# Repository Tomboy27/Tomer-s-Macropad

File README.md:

# Tomer's Macropad

This is a custom, programmable macropad powered by a Seeed Studio XIAO RP2040, KMK firmware, a custom PCB, and a 3D-printed case. This is my first hardware project, completed to improve both my engineering skills and my day to day life with shortcuts and a rotary encoder.

## What It Does

- 6 mechanical keys with Cherry MX switches and DSA keycaps
- Rotary encoder (EC11) for volume up/down and mute
- Custom firmware using KMK (CircuitPython-based mechanical keyboard firmware)
- PC-side macros for application-specific shortcuts
- Custom PCB and 3D-printed case

## Bill of Materials

- 6× Cherry MX Switches
- 6× DSA keycaps
- 1× Seeed Studio XIAO RP2040
- 4× 1N4148 diodes (through-hole)
- 1× EC11 rotary encoder
- 4× M3×16mm screws
- 1× case (2 printed parts, STEP file in `CAD/`)

## Features

### Firmware

- One primary layer with 7 keys: A, B, C, D, E, F, and MUTE
- Rotary encoder:
  - Turn clockwise for volume up (`KC.VOLU`)
  - Turn counter-clockwise for volume down (`KC.VOLD`)

### PC Macros

- Custom macros configured on my PC for workflow shortcuts such as an auto clicker, opening certain apps, etc.

## Hardware

### Wiring

- See wiring diagrams below!
- The XIAO RP2040 is used as the main microcontroller.
- Keys are wired with diodes and directly to GPIO pins.
- Rotary encoder is wired to `GP0` (A) and `GP1` (B).

### PCB

- Custom PCB designed for the macropad.
- Screenshot of the PCB layout is shown below.

### Case

- 3D-printed case made of two parts.
- STEP file available in `CAD/`.
- Assembly uses 4× M3×16mm screws.

## Assembly / Build Steps

Coming Soon...

## Firmware

- Written in CircuitPython using the KMK library.
- Main file: `macropad.py` in the repo root.
- Keymap: 1 layer with 7 inputs (6 keys + encoder button).
- Encoder actions: volume up/down.

To flash:

1. Put the XIAO RP2040 in bootloader mode (double-press reset or connect BOOT0).
2. Copy `macropad.py` to the `CIRCUITPY` drive.
3. Ensure the `KMK` library is installed on the CIRCUITPY drive.

## Lessons Learned

- First hardware project: learned PCB layout, soldering, and embedded firmware for mechanical keyboards using KMK and CircuitPython.
- Discovered how rotary encoders work and how to integrate them into KMK firmware.
- Improved Github skills (first repo as well!)
- Overall increase in problem solving through the many issues that came with the building process.

## Future Improvements

- Add a second firmware layer for app-specific shortcuts.
- Add an OLED display.
- Improve the keymap with more complex macros in the firmware instead of PC-side macros.
- Document the build process with more photos and quantitative test results (e.g., debounce behavior, latency).

## Photos

Here is a picture of the final HackPad, schematic, PCB, and case model!

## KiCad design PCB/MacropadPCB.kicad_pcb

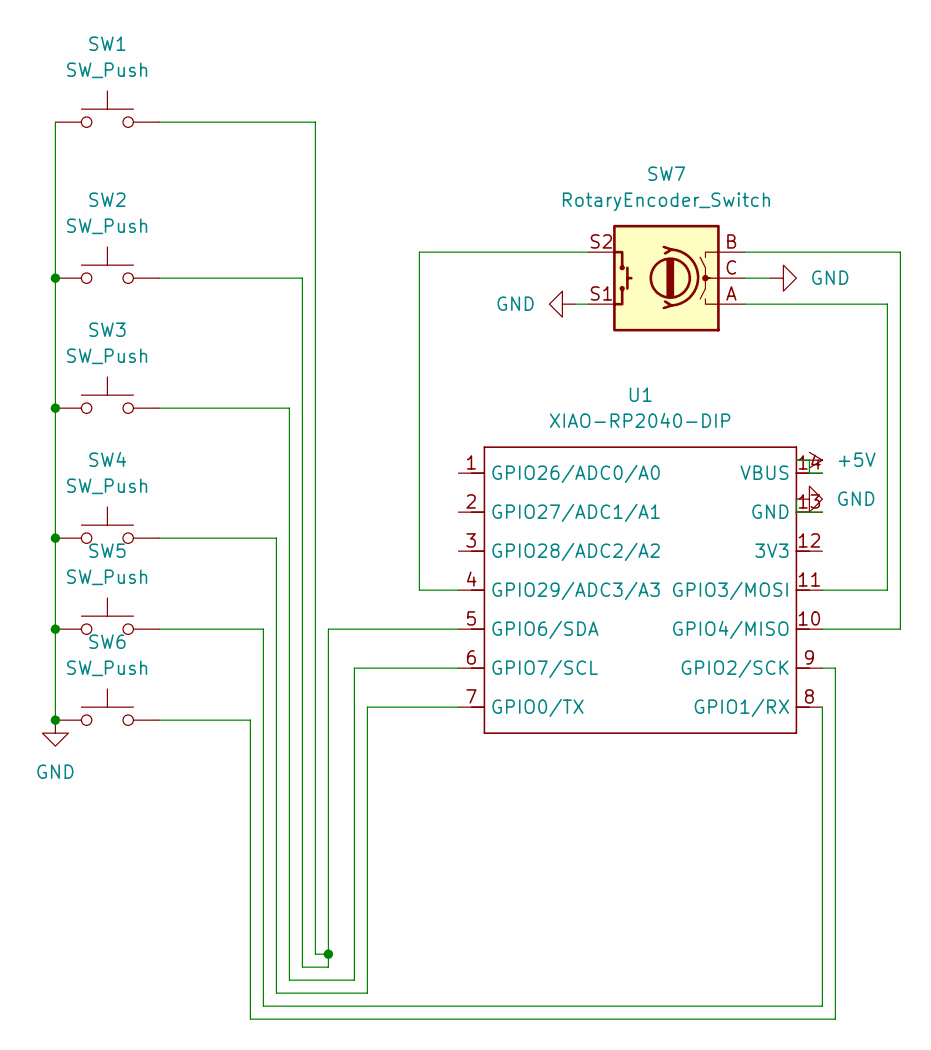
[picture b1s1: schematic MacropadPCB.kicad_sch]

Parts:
SW1, SW2, SW3, SW4, SW5, SW6: SW_Push; SW_Cherry_MX_1.00u_PCB
SW7: RotaryEncoder_Switch; RotaryEncoder_Alps_EC11E-Switch_Vertical_H20mm
U1: XIAO-RP2040-DIP

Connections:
+5V: U1.14 (VBUS)
GND: SW1.1, SW2.1, SW3.1, SW4.1, SW5.1, SW6.1, SW7.C, SW7.S1, U1.13 (GND)
unnamed: SW4.2, U1.7 (GPIO0/TX)
unnamed: SW5.2, U1.8 (GPIO1/RX)
unnamed: SW6.2, U1.9 (GPIO2/SCK)
unnamed: SW7.A, U1.11 (GPIO3/MOSI)
unnamed: SW7.B, U1.10 (GPIO4/MISO)
unnamed: SW1.2, SW2.2, U1.5 (GPIO6/SDA)
unnamed: SW3.2, U1.6 (GPIO7/SCL)
unnamed: SW7.S2, U1.4 (GPIO29/ADC3/A3)

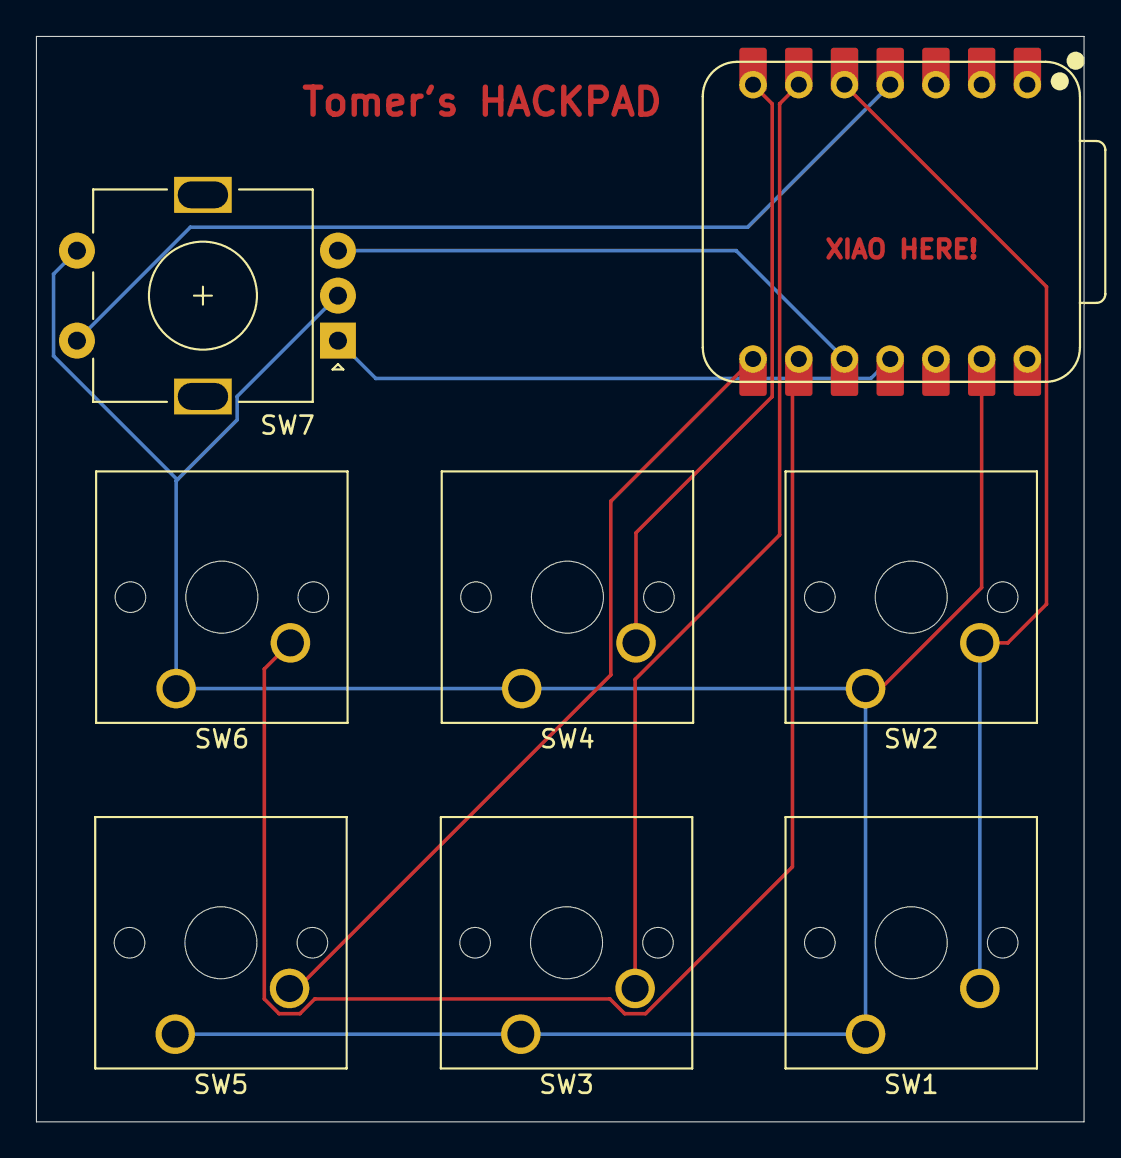
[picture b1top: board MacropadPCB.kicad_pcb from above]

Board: 2 copper layers, 58.2 x 60.3 mm, 8 parts (0 on the bottom side), 9 nets.

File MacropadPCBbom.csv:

"Reference","Qty","Value","DNP","Exclude from BOM","Exclude from Board","Footprint","Datasheet"
"SW1,SW2,SW3,SW4,SW5,SW6","6","SW_Push","","","","Button_Switch_Keyboard:SW_Cherry_MX_1.00u_PCB","~"
"SW7","1","RotaryEncoder_Switch","","","","Rotary_Encoder:RotaryEncoder_Alps_EC11E-Switch_Vertical_H20mm","~"
"U1","1","XIAO-RP2040-DIP","","","","MacroPadPCB:XIAO-RP2040-DIP",""

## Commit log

2025-11-27 Adding the initial PCB files
2025-12-02 moved README
2025-12-02 picture update
2025-12-02 picture fix
2025-12-06 VERSION 3
2025-12-06 gerber and csv
